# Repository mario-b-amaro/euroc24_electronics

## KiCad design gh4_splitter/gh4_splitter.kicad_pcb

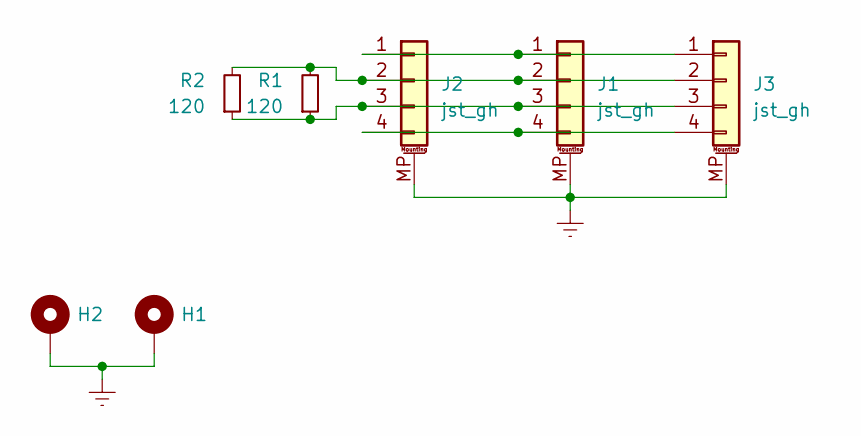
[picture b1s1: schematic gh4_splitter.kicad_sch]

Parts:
H1, H2: MountingHole_Pad; MountingHole_2.2mm_M2_ISO14580_Pad
J1, J2, J3: jst_gh; JST_GH_BM04B-GHS-TBT_1x04-1MP_P1.25mm_Vertical
R1, R2: 120; R_0603_1608Metric_Pad0.98x0.95mm_HandSolder

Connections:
Earth: H1.1, H2.1, J1.MP (MountPin), J2.MP (MountPin), J3.MP (MountPin)
unnamed: J1.1, J2.1, J3.1
unnamed: J1.2, J2.2, J3.2, R1.2, R2.2
unnamed: J1.3, J2.3, J3.3, R1.1, R2.1
unnamed: J1.4, J2.4, J3.4

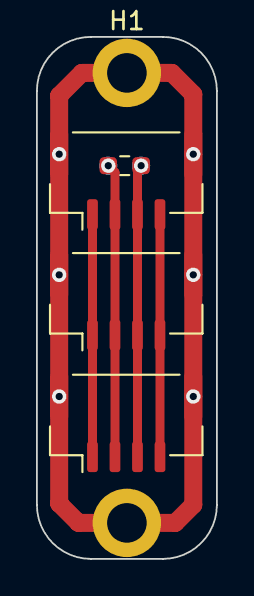
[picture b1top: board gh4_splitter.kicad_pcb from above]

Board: 2 copper layers, 10.0 x 29.0 mm, 7 parts (1 on the bottom side), 5 nets.

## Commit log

2023-11-04 add gh4 splitter
2023-11-23 first simulation
2023-11-23 migrate to ipynb
2024-02-02 new version
2024-02-07 latest version
2024-02-17 update rocketpy
2024-02-21 Updated Freyja OpenRocket (15cm)
2024-02-25 Updated Freyja OpenRocket
2024-02-27 updates 25/02/2024
